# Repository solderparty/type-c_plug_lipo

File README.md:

# 3.7V/4.2V LiPo Battery Charger with USB Type-C Plug

A simple breakout board for the ME4055-N LiPo charger.

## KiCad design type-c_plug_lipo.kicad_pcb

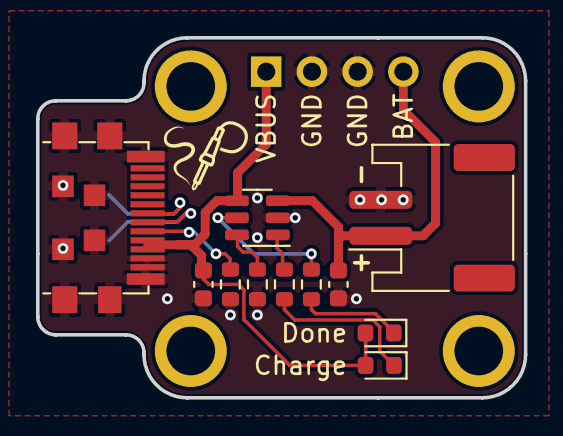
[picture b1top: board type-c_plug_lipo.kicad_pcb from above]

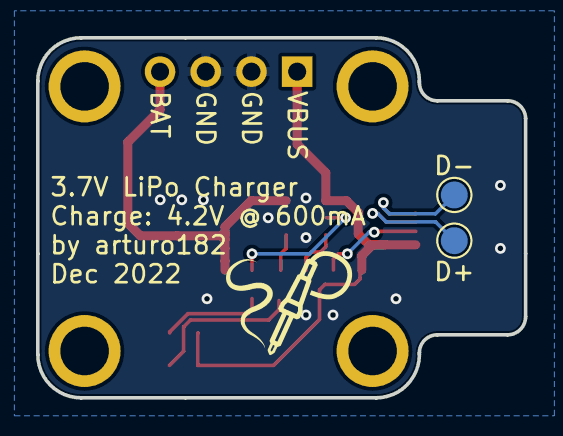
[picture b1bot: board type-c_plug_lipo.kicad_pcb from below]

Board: 2 copper layers, 27.1 x 20.0 mm, 14 parts (2 on the bottom side), 11 nets.

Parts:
C1, C2: 10uF; C_0603_1608Metric
D1: LED_CHR; LED_0603_1608Metric
D2: LED_DONE; LED_0603_1608Metric
J1: Conn_Battery; JST_PH_S2B-PH-SM4-TB_1x02-1MP_P2.00mm_Horizontal
J2: USB_C_Plug_USB2.0; USB_C_Plug_UTC009-C12
J4: Conn_Pwr; PinHeader_1x04_P2.54mm_Vertical
R1: 5.1K; R_0603_1608Metric
R2: 2K; R_0603_1608Metric
R3, R4: 1K; R_0603_1608Metric
TP1: TP_D-; TestPoint_Pad_D1.5mm
TP2: TP_D+; TestPoint_Pad_D1.5mm
U1: ME4055-N; SOT-23-6

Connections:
+BATT: C2.2, J1.1, J4.4, U1.3 (VBAT)
/D+: J2.A6 (D+), TP2.1
/D-: J2.A7 (D-), TP1.1
GND: C1.1, C2.1, J1.2, J2.A1 (GND), J2.B12 (GND), J2.S1 (SHIELD), J4.2, J4.3, R1.1, R2.1, U1.2 (GND)
unnamed: D1.1 (K), R3.2
unnamed: D2.1 (K), R4.2
unnamed: J2.A5 (CC), R1.2
unnamed: R2.2, U1.6 (PROG)
unnamed: R3.1, U1.1 (STAT)
unnamed: R4.1, U1.5 (DONE)
VBUS: C1.2, D1.2 (A), D2.2 (A), J2.A4 (VBUS), J2.B9 (VBUS), J4.1, U1.4 (VDD)

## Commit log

2021-02-03 Initial import
2023-03-19 Rev 2
